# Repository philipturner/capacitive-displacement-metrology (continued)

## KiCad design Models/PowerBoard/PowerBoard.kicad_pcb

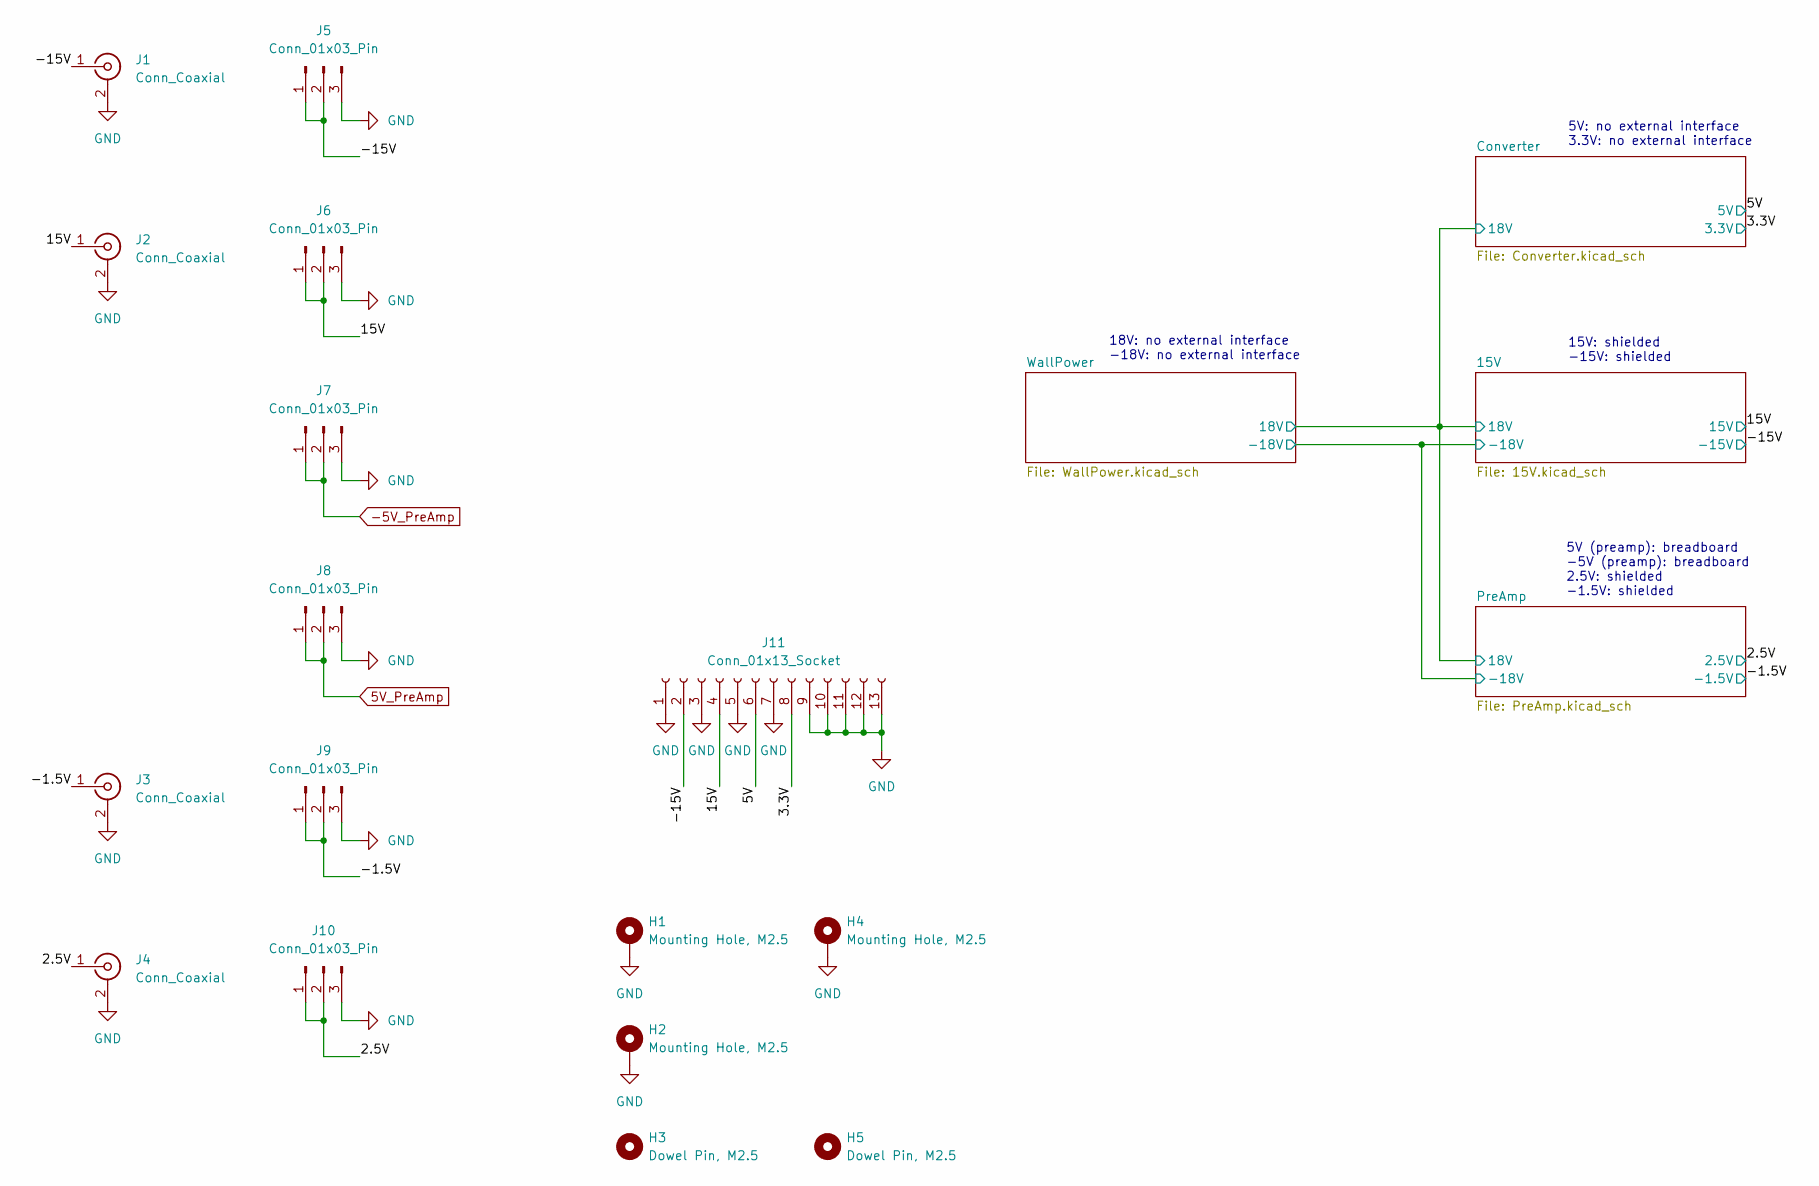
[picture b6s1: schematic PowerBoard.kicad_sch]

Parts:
H1, H2, H4: Mounting Hole, M2.5; Keystone_24929
H3, H5: Dowel Pin, M2.5; DowelPin_2.5mm
J1, J2, J3, J4: Conn_Coaxial; Molex_MCX
J5, J6, J7, J8, J9, J10: Conn_01x03_Pin; PinHeader_1x3
J11: Conn_01x13_Socket; PinSocket_1x13

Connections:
5V_PreAmp: J8.1, J8.2; also elsewhere on the board
-5V_PreAmp: J7.1, J7.2; also elsewhere on the board
/2.5V: J4.1 (In), J10.1, J10.2; also elsewhere on the board
/3.3V: J11.8; also elsewhere on the board
/5V: J11.6; also elsewhere on the board
/15V: J2.1 (In), J6.1, J6.2, J11.4; also elsewhere on the board
/-1.5V: J3.1 (In), J9.1, J9.2; also elsewhere on the board
/-15V: J1.1 (In), J5.1, J5.2, J11.2; also elsewhere on the board
GND: H1.1, H2.1, H4.1, J1.2 (Ext), J2.2 (Ext), J3.2 (Ext), J4.2 (Ext), J5.3, J6.3, J7.3, J8.3, J9.3, J10.3, J11.1, J11.3, J11.5, J11.7, J11.9, J11.10, J11.11, J11.12, J11.13; also elsewhere on the board

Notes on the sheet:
18V: no external interface -18V: no external interface
5V (preamp): breadboard -5V (preamp): breadboard 2.5V: shielded -1.5V: shielded
15V: shielded -15V: shielded
5V: no external interface 3.3V: no external interface

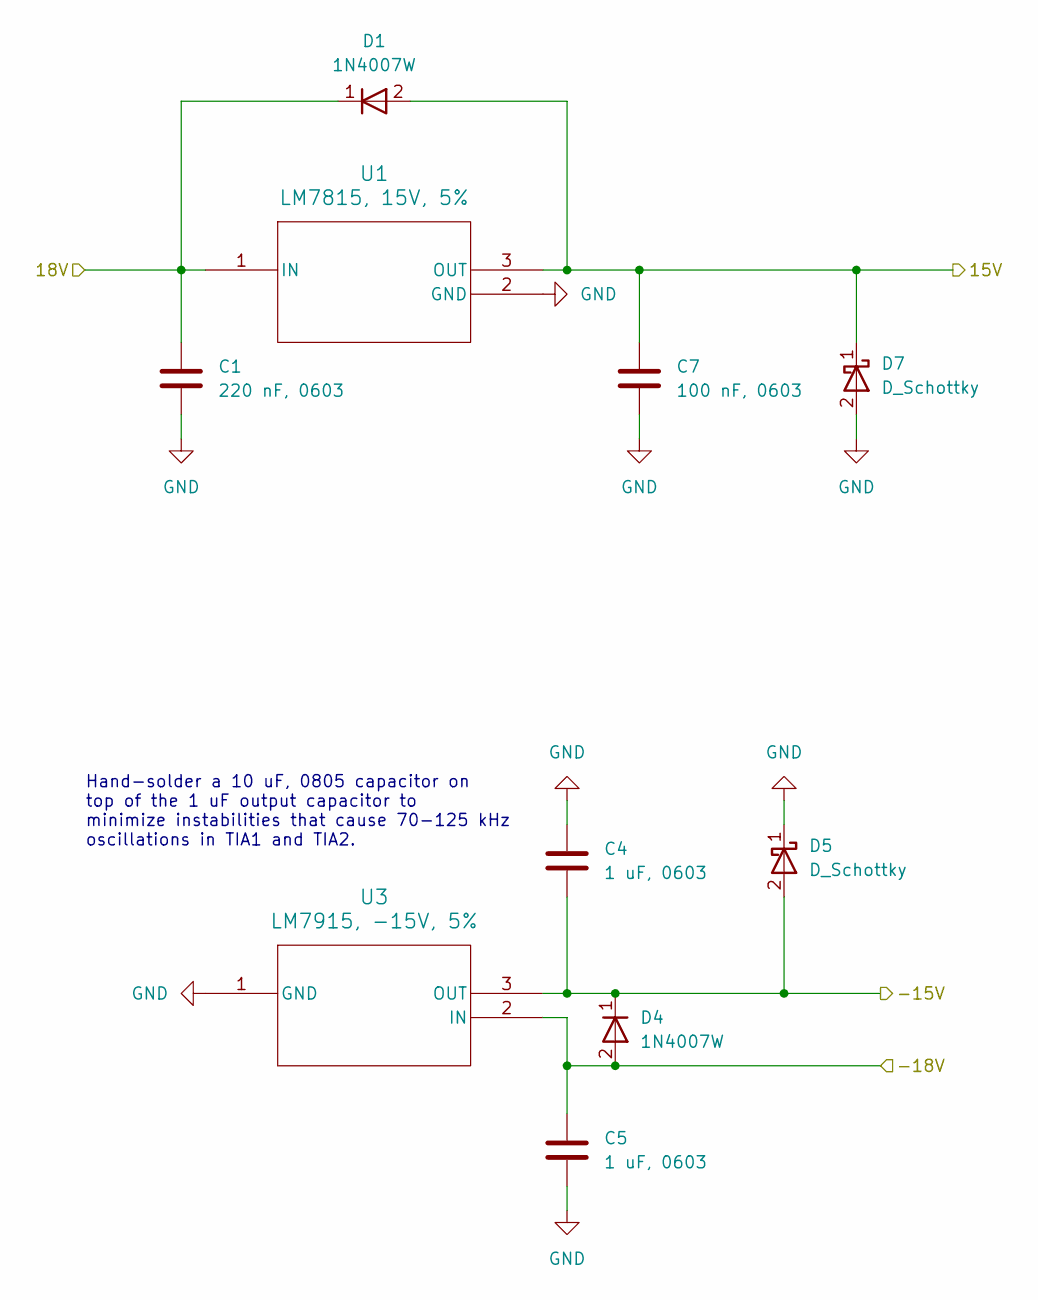
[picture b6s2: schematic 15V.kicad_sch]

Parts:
C1: 220 nF, 0603; CAPC0603
C4, C5: 1 uF, 0603; CAPC0603
C7: 100 nF, 0603; CAPC0603
D1, D4: 1N4007W; SOD-123FL
D5, D7: D_Schottky; SOD-123
U1: LM7815, 15V, 5%; TO-220
U3: LM7915, -15V, 5%; TO-220

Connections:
/15V: C7.1, D1.2 (A), D7.1 (K), U1.3 (OUT); also elsewhere on the board
/15V/18V: C1.1, D1.1 (K), U1.1 (IN); also elsewhere on the board
/15V/-18V: C5.1, D4.2 (A), U3.2 (IN); also elsewhere on the board
/-15V: C4.2, D4.1 (K), D5.2 (A), U3.3 (OUT); also elsewhere on the board
GND: C1.2, C4.1, C5.2, C7.2, D5.1 (K), D7.2 (A), U1.2 (GND), U3.1 (GND); also elsewhere on the board

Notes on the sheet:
Hand-solder a 10 uF, 0805 capacitor on top of the 1 uF output capacitor to minimize instabilities that cause 70-125 kHz oscillations in TIA1 and TIA2.

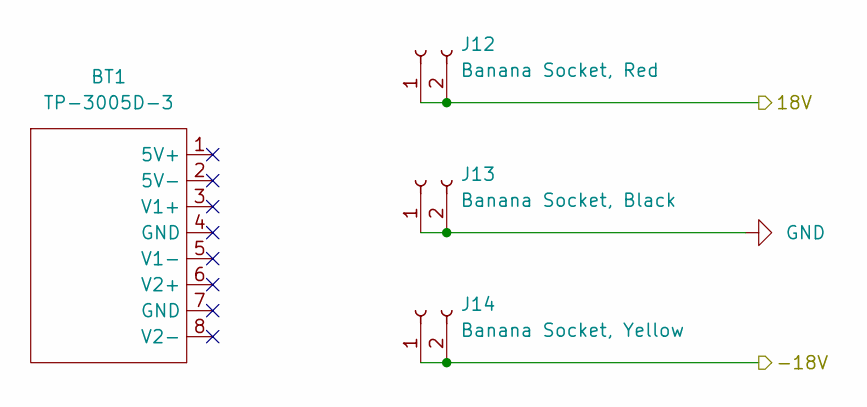
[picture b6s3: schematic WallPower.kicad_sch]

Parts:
BT1: TP-3005D-3
J12: Banana Socket, Red; Multicomp_24.243
J13: Banana Socket, Black; Multicomp_24.243
J14: Banana Socket, Yellow; Multicomp_24.243

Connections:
/15V/18V: J12.1, J12.2; also elsewhere on the board
/15V/-18V: J14.1, J14.2; also elsewhere on the board
GND: J13.1, J13.2; also elsewhere on the board

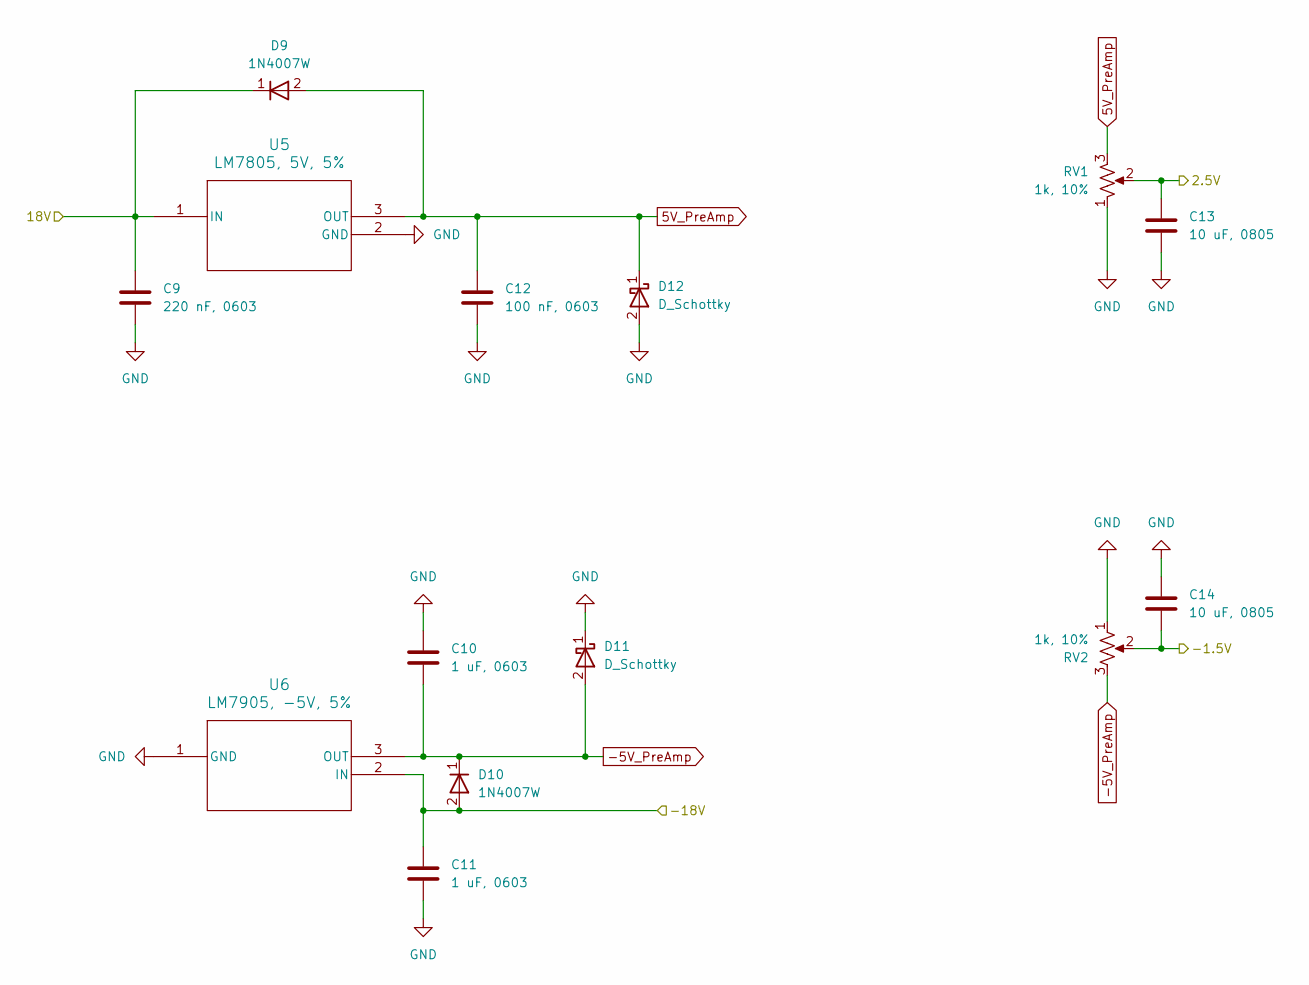
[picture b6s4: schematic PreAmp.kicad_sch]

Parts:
C9: 220 nF, 0603; CAPC0603
C10, C11: 1 uF, 0603; CAPC0603
C12: 100 nF, 0603; CAPC0603
C13, C14: 10 uF, 0805; CAPC0805
D9, D10: 1N4007W; SOD-123FL
D11, D12: D_Schottky; SOD-123
RV1, RV2: 1k, 10%; Bourns_3296Y
U5: LM7805, 5V, 5%; TO-220
U6: LM7905, -5V, 5%; TO-220

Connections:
5V_PreAmp: C12.1, D9.2 (A), D12.1 (K), RV1.3, U5.3 (OUT); also elsewhere on the board
-5V_PreAmp: C10.2, D10.1 (K), D11.2 (A), RV2.3, U6.3 (OUT); also elsewhere on the board
/2.5V: C13.1, RV1.2; also elsewhere on the board
/15V/18V: C9.1, D9.1 (K), U5.1 (IN); also elsewhere on the board
/15V/-18V: C11.1, D10.2 (A), U6.2 (IN); also elsewhere on the board
/-1.5V: C14.2, RV2.2; also elsewhere on the board
GND: C9.2, C10.1, C11.2, C12.2, C13.2, C14.1, D11.1 (K), D12.2 (A), RV1.1, RV2.1, U5.2 (GND), U6.1 (GND); also elsewhere on the board

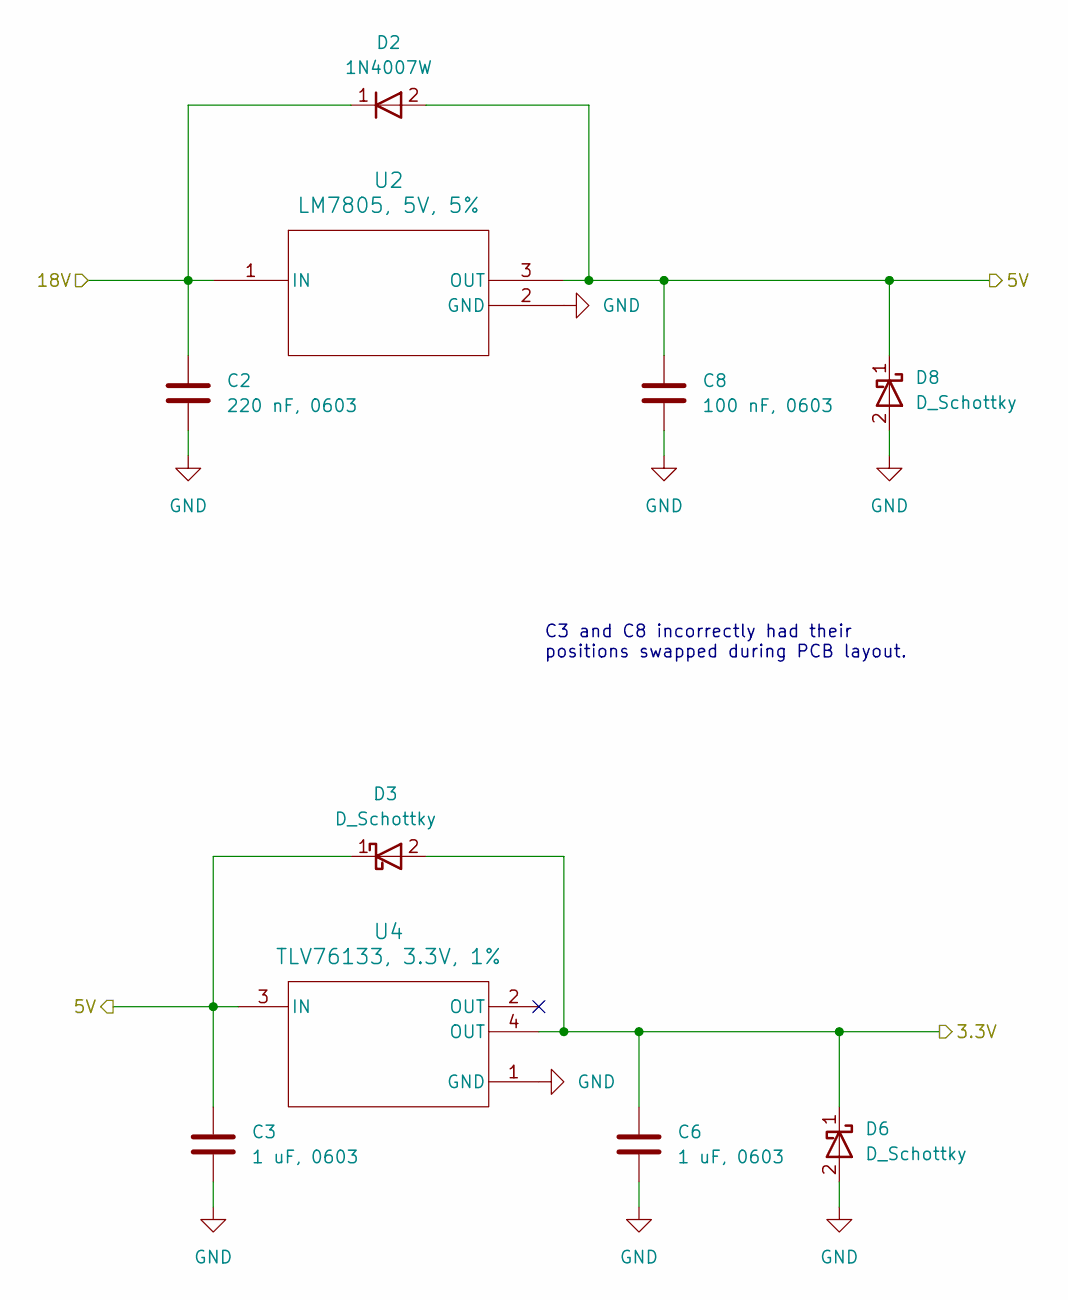
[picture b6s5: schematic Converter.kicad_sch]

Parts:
C2: 220 nF, 0603; CAPC0603
C3, C6: 1 uF, 0603; CAPC0603
C8: 100 nF, 0603; CAPC0603
D2: 1N4007W; SOD-123FL
D3, D6, D8: D_Schottky; SOD-123
U2: LM7805, 5V, 5%; TO-220
U4: TLV76133, 3.3V, 1%; SOT-223

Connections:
/3.3V: C6.1, D3.2 (A), D6.1 (K), U4.4 (OUT); also elsewhere on the board
/5V: C3.1, C8.1, D2.2 (A), D3.1 (K), D8.1 (K), U2.3 (OUT), U4.3 (IN); also elsewhere on the board
/15V/18V: C2.1, D2.1 (K), U2.1 (IN); also elsewhere on the board
GND: C2.2, C3.2, C6.2, C8.2, D6.2 (A), D8.2 (A), U2.2 (GND), U4.1 (GND); also elsewhere on the board

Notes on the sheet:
C3 and C8 incorrectly had their positions swapped during PCB layout.

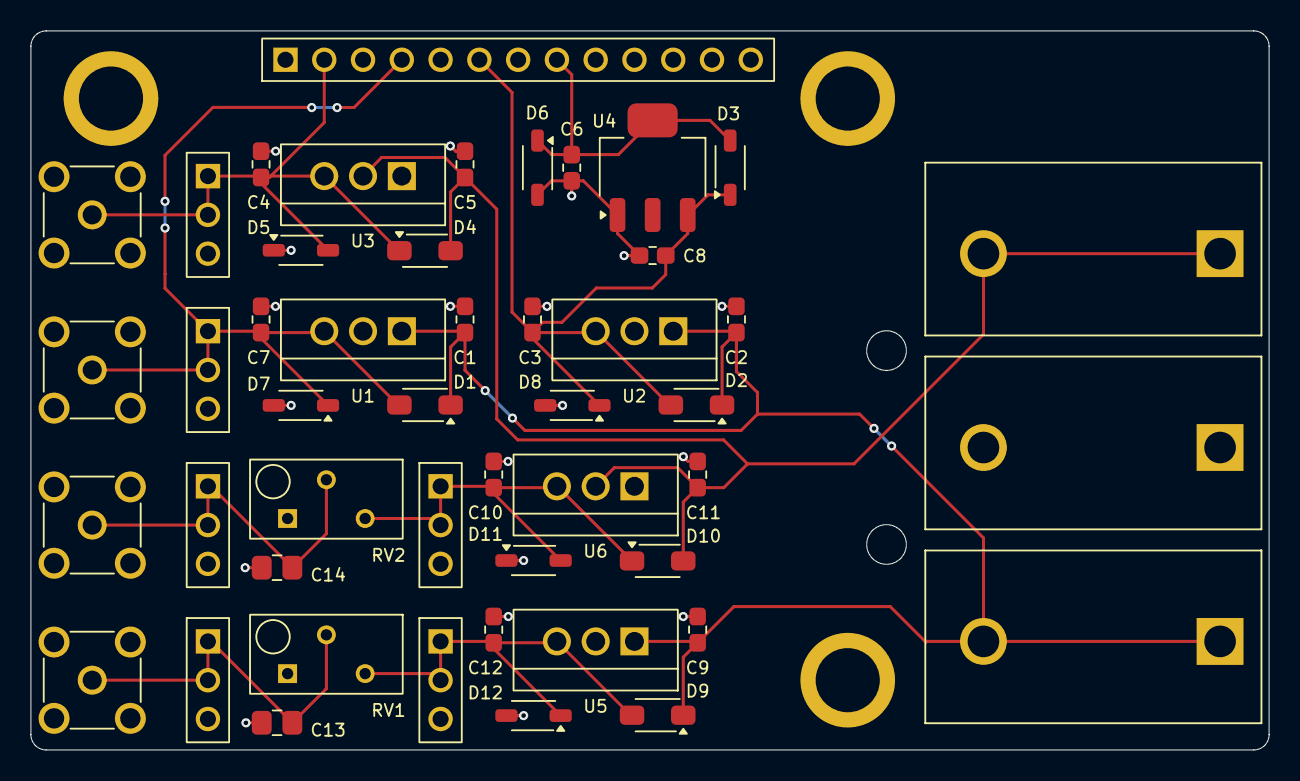
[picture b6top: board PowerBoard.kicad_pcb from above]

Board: 2 copper layers, 81.1 x 47.1 mm, 53 parts (0 on the bottom side), 11 nets.

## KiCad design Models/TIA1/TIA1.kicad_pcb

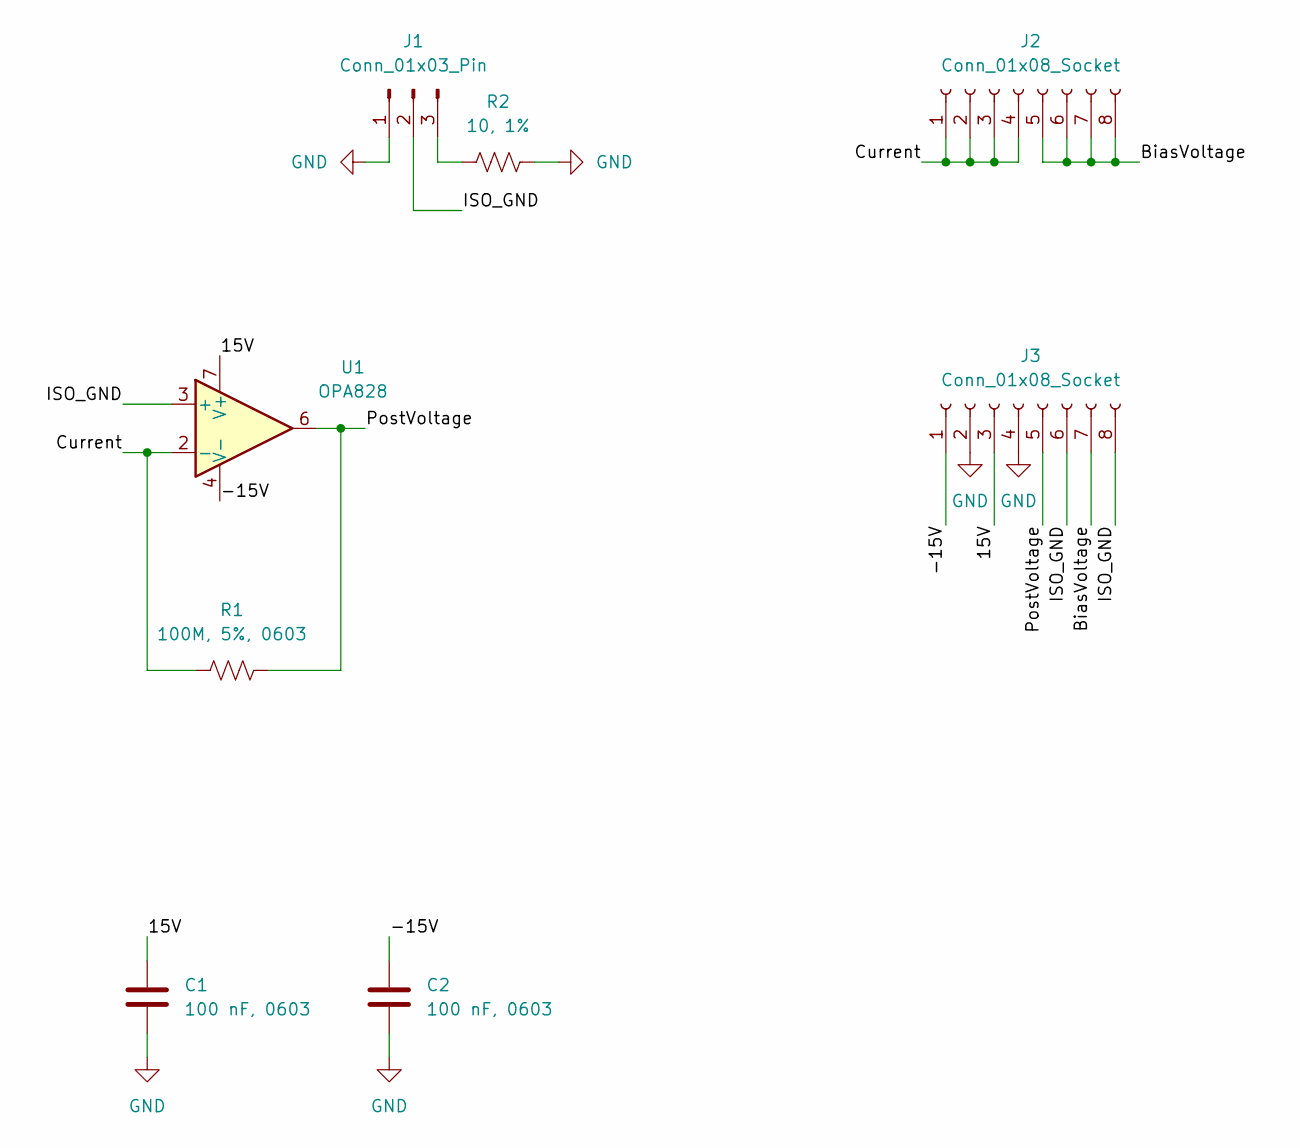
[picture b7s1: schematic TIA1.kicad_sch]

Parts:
C1, C2: 100 nF, 0603; CAPC0603
J1: Conn_01x03_Pin; PinHeader_1x3
J2, J3: Conn_01x08_Socket; PinSocket_1x8
R1: 100M, 5%, 0603; RESC0603
R2: 10, 1%; RESC0603
U1: OPA828; SOIC-8

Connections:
/15V: C1.1, J3.3, U1.7 (V+)
/-15V: C2.1, J3.1, U1.4 (V-)
/BiasVoltage: J2.5, J2.6, J2.7, J2.8, J3.7
/Current: J2.1, J2.2, J2.3, J2.4, R1.1, U1.2 (-)
/ISO_GND: J1.2, J3.6, J3.8, U1.3 (+)
/PostVoltage: J3.5, R1.2, U1.6
GND: C1.2, C2.2, J1.1, J3.2, J3.4, R2.2
unnamed: J1.3, R2.1

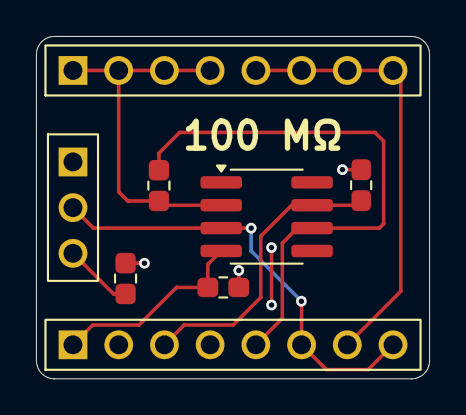
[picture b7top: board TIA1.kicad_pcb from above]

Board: 2 copper layers, 21.8 x 19.0 mm, 8 parts (0 on the bottom side), 8 nets.

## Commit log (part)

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2026-04-30 Refactor the tone duration to not be hard-coded
2026-04-30 Save progress
2026-05-01 Upload media
2026-05-04 Important note on the README
2026-05-04 Removed unused code
2026-05-04 This code works very well
2026-05-04 We need something better than teleplot.
2026-05-05 Add more stuff to gitignore
2026-05-05 Test gitignore
2026-05-05 Working on stuff
2026-05-05 Fix gitignore
2026-05-05 Getting better
2026-05-05 Continue this tomorrow
2026-05-06 Looking good so far
2026-05-07 Save progress debugging
2026-05-07 This code works
2026-05-07 Some data about unreliability of serial link
2026-05-08 It all just kind of works
2026-05-08 Need to optimize the host code
2026-05-08 Will attempt to refactor how partial entries are processed
2026-05-08 We have enough data to start making conclusions
2026-05-11 New script
2026-05-11 what is happening with git commits
2026-05-11 The code no longer has major issues for streaming serial data from Teensy to PC
2026-05-11 This works very well
2026-05-11 This is some good progress
2026-05-12 Now generating a fake waveform
2026-05-12 Improving
2026-05-12 Matplotllib is just too slow for this UI
2026-05-12 A good step
2026-05-12 Some progress
2026-05-12 The code is good as-is now
2026-05-13 This is very hard to make work
2026-05-13 This looks good, now we must clean up the code
2026-05-13 Plans for artificial oscilloscope functionality
2026-05-13 Implemented the threshold checker
2026-05-13 Narrowing down cause of concurrency <-> Python bug
2026-05-13 I really did try everything to fix this concurrency problem
2026-05-13 Looking good
2026-05-13 Ready to test the code
2026-05-14 Everything is now looking good
2026-05-14 There was a bug that created the alpha constant for 41 kHz loop instead of 83 kHz loop
2026-05-15 Why wont it save
2026-05-15 It seems that bugs from freezing on the host PC are fixed
2026-05-15 Code is completely cleaned up now
2026-05-15 Why wont git commits actually save files
2026-05-18 Numerical instability in the biquad filter, fixed it with FP64 for now
2026-05-20 Save progres
2026-05-20 We need to make a dedicated file for blind stepping
2026-05-20 Finish this another time
2026-05-21 Everything compiles now
2026-05-21 All of the code is drafted now
2026-05-22 Fix software bug that made it into the recording
2026-05-22 Improvements to the real-time renderer code
2026-05-22 We need to clean up the code after this debugging
2026-05-22 Getting something that looks like feedback
2026-05-22 I have an idea to solve the problem where stability is improved from exponentially higher repulsion at high currents
2026-05-25 We need an internal model of response to current spikes
2026-05-25 It is a bit difficult to manage multiple code changes simultaneously
2026-05-26 Implemented graceful closing of SerialInterface
2026-05-26 Capacitance tracking is fixed
2026-05-27 the new code works
2026-05-27 Starting to draft the spectroscopy command
2026-05-27 Why wont it commit
2026-05-28 This doesnt fail to upload
2026-05-28 Upload images
2026-05-30 Fix a bug
2026-05-30 Unfortunately I have to stop for tonight
2026-06-01 Add spreadsheet link
2026-06-02 Wonder how close this is to finished
2026-06-02 Added SimpleScanner
2026-06-02 Reordered some includes
2026-06-03 bug fixes
2026-06-03 Did the commits happen?
2026-06-03 Fix a bug in command parsing
2026-06-03 Implemented code for notch filter
2026-06-03 Test whether I can commit with bad wifi
2026-06-04 Refactored some code
2026-06-04 This file did not commit
2026-06-04 Finished updating the Teensy code
2026-06-04 serial emulation appears to be working
2026-06-04 More refactoring
2026-06-04 Much more refined
2026-06-04 Save this change to the Teensy code
2026-06-04 Refactoring
2026-06-05 why didnt it commit
2026-06-05 Working on refining the UI now
2026-06-06 Fixed a Teensy bug
2026-06-06 Improvements to SerialInterface
2026-06-08 Working through some refactoring
2026-06-08 Working on a lot of programming tasks simultaneously
2026-06-10 Cannot identify the cause of large disparities between the high-res and efficient model
2026-06-11 Debugging
2026-06-11 Delayed pixel writing works
2026-06-12 Getting somewhere
2026-06-12 Some more cleanups
2026-06-12 We have found the optimal design for the code
2026-06-12 A little bit of refactoring
2026-06-12 Implemented Sample
2026-06-12 Implemented Queue
2026-06-12 Check how this README looks on GitHub
2026-06-12 Beautiful refactorings to the Swift prototype of CreepFilter
2026-06-12 Finished implementing Filter
2026-06-12 Program is too slow on the Teensy
2026-06-13 Going to try a more manual memory management approach
2026-06-13 This is a step toward something
2026-06-13 First improvement of the script
2026-06-13 Implemented first optimization to arithmetic
2026-06-13 Implemented optimization 2
2026-06-13 Some refactoring
2026-06-14 Added creep filter to SerialInterface
2026-06-14 Cleaned up ImagingSettings
2026-06-14 Solved some problems with coding of the line extraction thread
2026-06-14 The code compiles now
2026-06-15 Need one more refinement to the code
2026-06-15 Done with the software engineering, ready to test this
2026-06-15 Don't forget this change
2026-06-15 Improvement to behavior of 12 Mbit/s USB serial
2026-06-15 Some changes to the transition logic
2026-06-16 Changes to spectroscopy
2026-06-16 There is a bug in the code for polynomial peak generation, at least for SimpleScanner
2026-06-17 Tomorrow I will test how the system behaves when its DACs are functioning correctly
2026-06-17 Test whether formatting is correct
2026-06-17 Finish formatting media
2026-06-17 Save data
2026-06-17 Why are these timestamps still here
2026-06-18 Changes to prepare for longer loop periods and tilt correction
2026-06-18 Finished debugging the change of kilohertz loop period
2026-06-18 Is this everything coded?
2026-06-18 Prevent implicit type promotion to double precision
2026-06-18 This looks ready to test
2026-06-19 Refactored the declarations of the python classes a bit
2026-06-19 Forgot to include this in the commit
2026-06-19 Progress, but an unexplained crash
2026-06-19 This might be a solution to a crash in the creep filter
2026-06-19 Just need to refine the handling of electronic time lag
2026-06-19 High resolution electronic time lag is working
2026-06-19 Done with this round of coding
2026-06-19 One more important change: need to enable rectangular STM imaging
2026-06-20 In the middle of heavy refactoring
2026-06-20 Finished drafting the Teensy code for now
2026-06-20 Finished drafting changes to host code
2026-06-21 Bugs when minor dimension exceeds major dimension
2026-06-21 We need to correct for scale dilation at large creep values
2026-06-21 This setting for scale correction gives the best results, although it's more of an art to tune this than a science
2026-06-21 Forgot to commit this change
2026-06-21 Need to reduce the systematic error in tilt estimation
2026-06-21 Working on improved code
2026-06-21 Ready to start testing stuff again
2026-06-21 Improvements to capacitance tracker
2026-06-22 Save calibration data for 8i,20,20,1
2026-06-22 Cleaned up the code after this round of investigation
2026-06-23 Fix a programming error that went un-noticed
2026-06-23 Wrong name for file
2026-06-23 Fix a typo that made it into the video
